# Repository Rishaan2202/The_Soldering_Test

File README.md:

# The_Soldering_Test
<h3> So this is a basic pcb, which has many kinda footprints in which we need to solder components, it has many basic and common footprints of SMT and THT devices, so that we could increase our soldering skills!!! </h3>
<br>
<br>

<h2> So here's the Schematic: </h2>
<br>

<br>
<br>

<h2> The PCB looks like this: </h2>
<br>

<br>
<h3> Front view </h3>
<br>

<h3> Back view </h3>
<br>

<br>
<br>

<h2> Here are the cart Pictures </h2>
<br>
<h3> The Parts' Cart: </h3>
<br>

<br>
<h3> The PCBs' Cart: </h3>

<br>
<br>

<h2> TYSM!!! </h2>

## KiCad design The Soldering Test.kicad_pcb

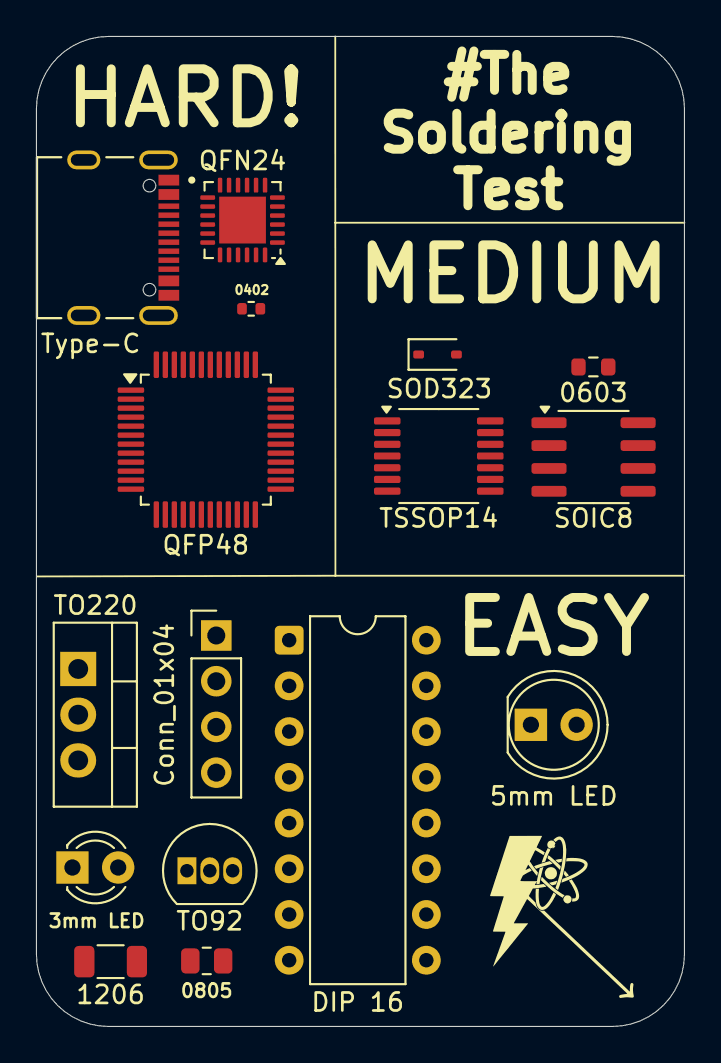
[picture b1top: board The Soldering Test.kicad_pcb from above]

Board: 2 copper layers, 36.0 x 55.0 mm, 16 parts (0 on the bottom side), 3 nets, no tracks yet.

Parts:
D1: 3mm LED; LED_D3.0mm
D2: 5mm LED; LED_D5.0mm
D3: SOD323; D_SOD-323
J2: KH-TYPE-C-16P; KINGHELM_KH-TYPE-C-16P
J3: Conn_01x04; PinHeader_1x04_P2.54mm_Vertical
R1: 0805; R_0805_2012Metric
R2: 1206; R_1206_3216Metric
R3: 0603; R_0603_1608Metric
R4: 0402; R_0402_1005Metric
U1: TO92; TO-92_Inline
U2: TSSOP14; TSSOP-14_4.4x5mm_P0.65mm
U3: SOIC8; SOIC-8_3.9x4.9mm_P1.27mm
U4: QFP48; TQFP-48_7x7mm_P0.5mm
U5: QFN24; QFN-24-1EP_4x4mm_P0.5mm_EP2.6x2.6mm
U8: DIP 16; DIP-16_W7.62mm
U9: TO220; TO-220-3_Vertical

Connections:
unnamed: U4.15 (GND), U4.29 (GND), U4.43 (GND)
unnamed: U4.14 (VDD), U4.42 (VDD)
unnamed: U5.2 (GND), U5.25 (GND)

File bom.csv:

Designator,Footprint,Quantity,Value,LCSC Part #
D1,LED_D3.0mm,1,3mm LED,C2895470
D2,LED_D5.0mm,1,5mm LED,C87271
D3,D_SOD-323,1,SOD323,C2128
J2,KINGHELM_KH-TYPE-C-16P,1,KH-TYPE-C-16P,C709357
J3,PinHeader_1x04_P2.54mm_Vertical,1,Conn_01x04,C5116483
R1,805,1,805,C96346
R2,1206,1,1206,C17902
R3,603,1,603,C109318
R4,402,1,402,C190119
U1,TO-92_Inline,1,TO92,C177006
U2,TSSOP-14_4.4x5mm_P0.65mm,1,TSSOP14,C52260201
U3,SOIC-8_3.9x4.9mm_P1.27mm,1,SOIC8,C7603386
U4,TQFP-48_7x7mm_P0.5mm,1,QFP48,C529329
U5,QFN-24-1EP_4x4mm_P0.5mm_EP2.6x2.6mm,1,QFN24,C45223
U8,DIP-16_W7.62mm,1,DIP 16,C18723506
U9,TO-220-3_Vertical,1,TO220,C22389993

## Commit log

2025-11-21 Enhance README with HTML and schematic images
    Updated README to include HTML formatting and images.
